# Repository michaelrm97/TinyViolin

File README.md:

# TinyViolin

This project aims to create a small, playable, electric violin. The components of this project are:
- Hardware: PCB design
- Housing: Housing for project, designed to be laser cut with 3mm plywood
- Software:
  * TinyViolin2 - Atmel Studio project which contains the code that runs with the onboard ATMega328 (written in C++ and makes extensive use of Arduino libraries)
  * TVLoader - Visual Studio project which contains code for converting midi files (written in C#)

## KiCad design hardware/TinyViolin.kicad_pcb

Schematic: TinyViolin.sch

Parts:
BT1: AAA; 2466; Part Number 2466
C1, C2: 22pF; C_0805_2012Metric_Pad1.15x1.40mm_HandSolder; Part Number CL21C220JBANNNC
C3, C7: 100nF; C_0805_2012Metric_Pad1.15x1.40mm_HandSolder; Part Number CL21B104JBCNNNC
C4, C5, C6: 22uF; C_0805_2012Metric_Pad1.15x1.40mm_HandSolder; Part Number CL21A226MPCLRNC
C10: 100uF; CP_Radial_D6.3mm_P2.50mm; Part Number ECE-A0JKS101
D2: LED; LED_0805_2012Metric_Pad1.15x1.40mm_HandSolder; Part Number LG R971-KN-1
D3, D4, D5, D6: LED; LED_D5.0mm
H1, H2, H3, H4, H5, H6: M3; MountingHole_3.2mm_M3
J1: ICSP; PinHeader_2x03_P2.54mm_Vertical; Part Number M20-9980346
J2: 503182-1852; MOLEX_503182-1852; Part Number 5031821852
L1: 2.2uH; L_1206_3216Metric_Pad1.42x1.75mm_HandSolder; Part Number LQM31PN2R2M00L
LS1: Speaker; SP-1605; Part Number SP-1605
R1: 1M; R_0805_2012Metric_Pad1.15x1.40mm_HandSolder; Part Number RMCF0805FT1M00
R2: 10k; R_0805_2012Metric_Pad1.15x1.40mm_HandSolder; Part Number RNCP0805FTD10K0
R3, R4, R5, R6, R7: 220; R_0805_2012Metric_Pad1.15x1.40mm_HandSolder; Part Number RMCF0805FT220R
RV1: R_POT; PTA4543; Part Number PTA4543-2015DPB103
SW1: SW_SPDT; MHS122; Part Number MHS122
SW2: Tactile; SW_1825910-7; Part Number 1825910-7
SW3, SW4, SW5, SW6: SW_Push; TL1105; Part Number TL1105BF160Q
TP1: VBT; TestPoint_Pad_D1.0mm
TP2: GND; TestPoint_Pad_D1.0mm
TP3: V3.3; TestPoint_Pad_D1.0mm
U1: ATmega328P-PU; DIP-28_W7.62mm_LongPads; Part Number ATMEGA328P-PU
U2: BOOST; SOT95P280X145-5N; Part Number TPS613221ADBVR
Y1: Crystal 8MHz; Crystal_HC49-U_Vertical; Part Number ABL-8.000MHZ-B2

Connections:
+3V3: C3.1, C5.1, C6.1, C7.1, J1.2, J2.4, R2.1, R3.1, RV1.1, TP3.1, U1.7 (VCC), U2.4
/BAT: BT1.1, SW1.1, TP1.1
/BAT1: C4.1, L1.1, SW1.2
/BOW: RV1.2, U1.23 (PC0)
/LED1: R4.1, U1.13 (PD7)
/LED2: R5.1, U1.11 (PD5)
/LED3: R6.1, U1.3 (PD1)
/LED4: R7.1, U1.2 (PD0)
/MISO: J1.1, J2.7, U1.18 (PB4)
/MOSI: J1.4, J2.3, U1.17 (PB3)
/PB1: SW3.1, U1.12 (PD6)
/PB2: SW4.1, U1.6 (PD4)
/PB3: SW5.1, U1.5 (PD3)
/PB4: SW6.1, U1.4 (PD2)
/SCK: J1.3, J2.5, U1.19 (PB5)
/SPEAKER: C10.1, U1.15 (PB1)
/SS: J2.2, U1.16 (PB2)
/VBOOST: L1.2, U2.1
/~RST: J1.5, R2.2, SW2.1, SW2.2, U1.1 (~RESET~/PC6)
GND: BT1.2, C1.2, C2.2, C3.2, C4.2, C5.2, C6.2, C7.2, D2.1, D3.1, D4.1, D5.1, D6.1, J1.6, J2.6, LS1.2, RV1.3, SW2.3, SW2.4, SW3.2, SW4.2, SW5.2, SW6.2, TP2.1, U1.8 (GND), U1.22 (GND), U2.2
unnamed: C1.1, R1.2, U1.10 (XTAL2/PB7), Y1.1
unnamed: C2.1, R1.1, U1.9 (XTAL1/PB6), Y1.2
unnamed: C10.2, LS1.1
unnamed: D2.2, R3.2
unnamed: D3.2, R4.2
unnamed: D4.2, R5.2
unnamed: D5.2, R6.2
unnamed: D6.2, R7.2
unnamed: J2.P1, J2.P2, J2.P3, J2.P4, J2.P5

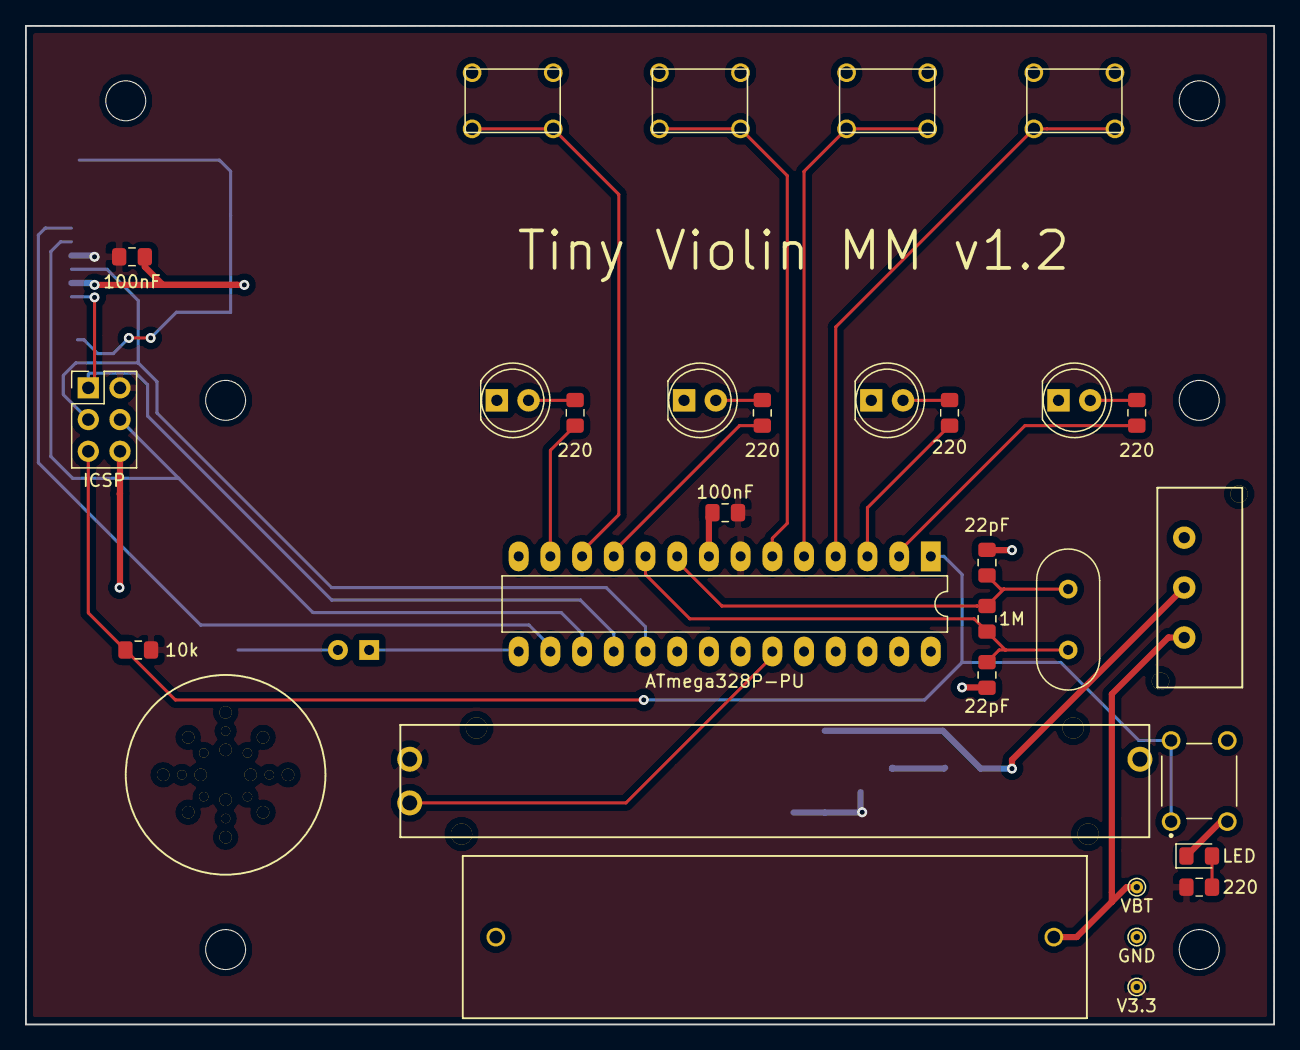
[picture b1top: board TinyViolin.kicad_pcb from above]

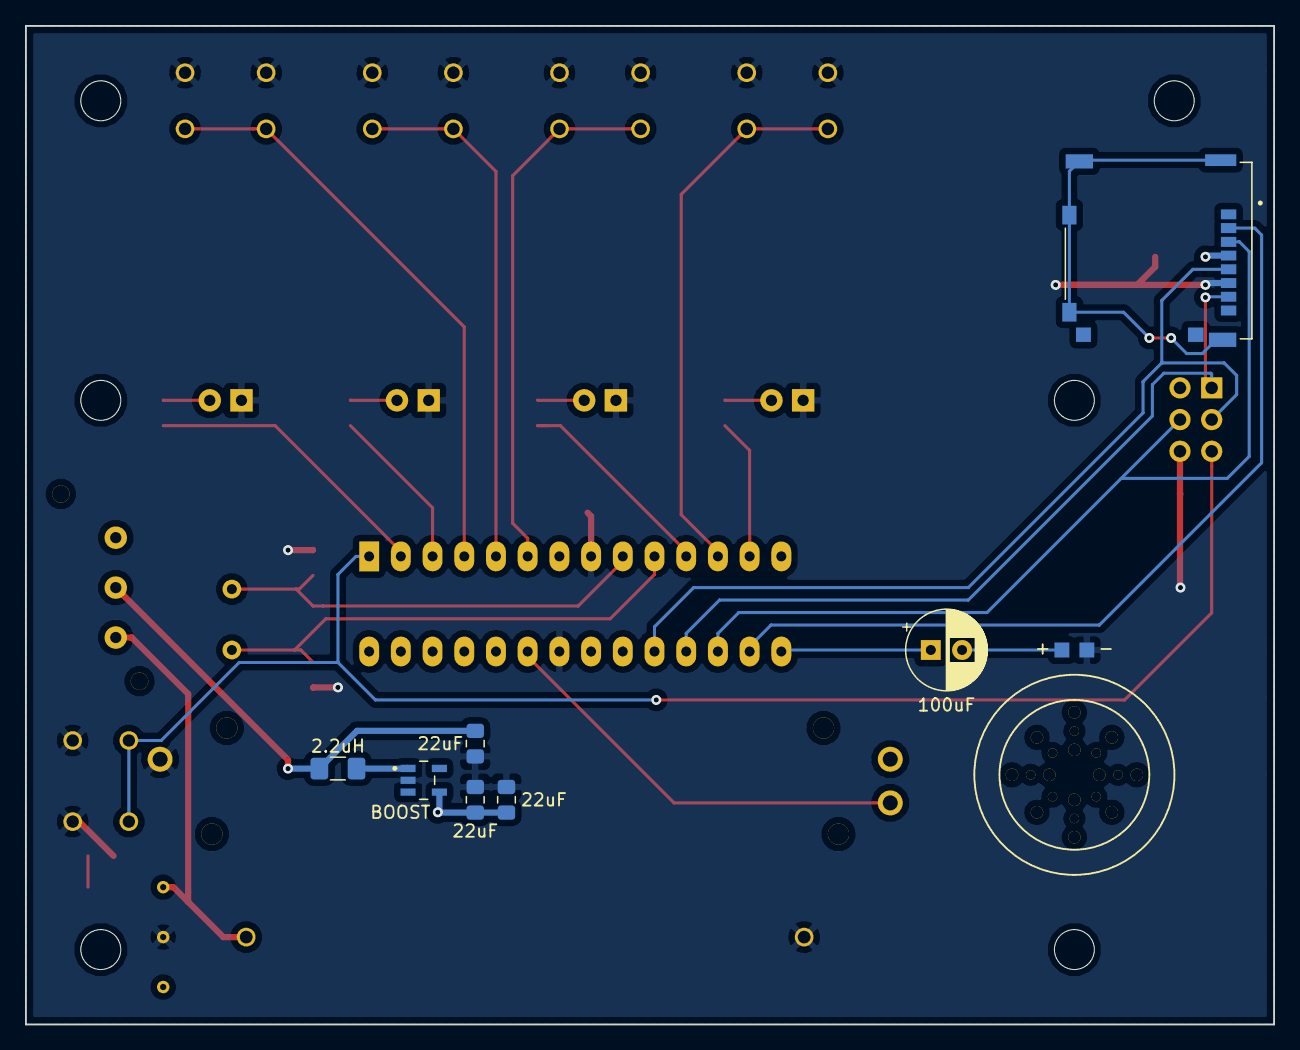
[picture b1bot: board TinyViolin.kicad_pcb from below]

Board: 2 copper layers, 100.0 x 80.0 mm, 44 parts (8 on the bottom side), 29 nets.

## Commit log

2019-10-17 Created project and started on PCB
2019-10-17 Changed power supply of LEDs to 5V
2019-10-18 Updated symbol fields
2019-10-21 Added all footprints
2019-10-21 Saved pcb
2019-10-26 Designed housing
2019-10-26 Moved violin body to the right
2019-10-26 Adjusted engraving on violin body
2019-10-26 Did pcb
2019-10-26 Moved icsp header up
2019-10-26 Fixed labels
2019-10-26 Adjusted violin body shape
2019-10-26 Created atmel studio project
2019-10-26 Wrote code for buttons and leds
2019-10-27 Implemented songs and main interrupt handler
2019-10-27 Updated crotchet period
2019-10-27 Moved holes and leds 1mm to the left
2019-10-28 Created dxf file
2019-10-30 Converted lines to format needed by laser cutter
2019-10-31 Updated pcb for manufacture
2019-10-31 Added gitignore for Gerber files
2019-11-03 Made uC code more object oriented
2019-11-03 Created loader program
2019-11-06 Implemented writing of notes to file
2019-11-07 Added colours to leds
2019-11-07 Added test mode for song
2019-11-12 Updated pcb with fixes
2019-11-12 Connected 3.3V to SD card
2019-11-13 Got music and SD card working
2019-11-13 Updating housing
2019-11-13 Prepared pcb for re-manufacturing
2019-11-15 Updated code with leds and buttons
2019-11-19 Got main thing working
2019-11-20 Reduced size of bow pot hole
2019-11-20 Changed battery on PCB
2019-11-20 Updated clock frequency
2019-11-21 Updated components
2019-11-21 Updated PCB and housing for re-re-manufacture
2019-11-21 Implemented duration for different tempos
2019-11-23 Made console version of loader
2019-11-26 Added pwm for LED and adjusted pot thresholds
2019-11-26 Fixed leds not turning on on error and release clock speed
2019-11-26 Fixed offsets in certain scales and switching notes
2019-11-26 Reduced brightness of LEDs on error
2019-11-29 Fixed issue with loading certain songs
2019-12-11 Improved bowing for short notes
